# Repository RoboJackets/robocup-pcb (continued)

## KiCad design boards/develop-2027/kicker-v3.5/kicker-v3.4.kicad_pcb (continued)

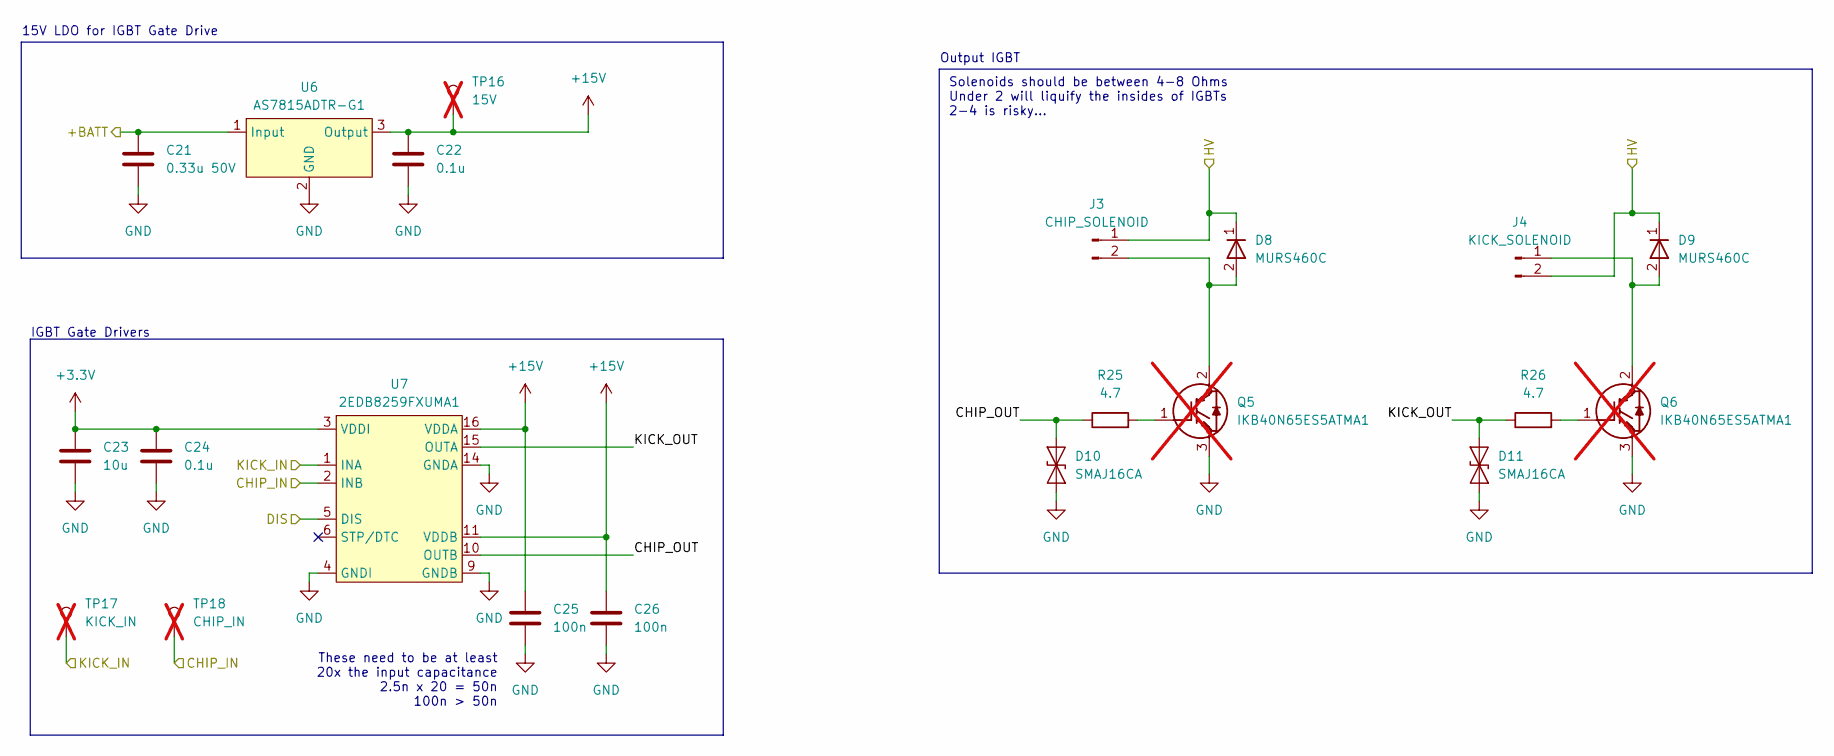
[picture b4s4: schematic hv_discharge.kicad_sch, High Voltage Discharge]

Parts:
C21: 0.33u 50V; C_0603_1608Metric; Manufacturer P/N 0603B334K500CT; LCSC P/N C296028
C22, C24: 0.1u; C_0603_1608Metric; Manufacturer P/N CL10B104KB8NNNC; LCSC P/N C1591
C23: 10u; C_0603_1608Metric; Manufacturer P/N GRM188R61E106MA73D; LCSC P/N C91606
C25, C26: 100n; C_0603_1608Metric; Manufacturer P/N CL10B104KB8NNNC; LCSC P/N C1591
D8, D9: MURS460C; D_SMC; Manufacturer P/N MURS460C; LCSC P/N C5249144
D10, D11: SMAJ16CA; D_SMA; Manufacturer P/N SMAJ16CA; LCSC P/N C19077537
J3: CHIP_SOLENOID; JST_PH_B2B-PH-K_1x02_P2.00mm_Vertical; Manufacturer P/N JST S2B-PH-K-S-GW; LCSC P/N C131337
J4: KICK_SOLENOID; JST_PH_B2B-PH-K_1x02_P2.00mm_Vertical; Manufacturer P/N JST S2B-PH-K-S-GW; LCSC P/N C131337
Q5, Q6: IKB40N65ES5ATMA1; TO-263-2; Manufacturer P/N IKB40N65ES5ATMA1; not fitted
R25, R26: 4.7; R_0603_1608Metric; Manufacturer P/N RC0603FR-074R7L; LCSC P/N C137705
TP16: 15V; TestPoint_Pad_D1.0mm; not fitted
TP17: KICK_IN; TestPoint_Pad_D1.0mm; not fitted
TP18: CHIP_IN; TestPoint_Pad_D1.0mm; not fitted
U6: AS7815ADTR-G1; TO-252-2; Manufacturer P/N AS7815ADTR-G1; LCSC P/N C460417
U7: 2EDB8259FXUMA1; SOIC-16_3.9x9.9mm_P1.27mm; Manufacturer P/N 2EDB8259FXUMA1; LCSC P/N C17317654

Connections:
+3.3V: C23.1, C24.1, U7.3 (VDDI), U7.8 (VDDI); also elsewhere on the board
+15V: C22.1, C25.1, C26.1, TP16.1 (1_1), U6.3 (Output), U7.11 (VDDB), U7.16 (VDDA)
+BATT: C21.1, U6.1 (Input); also elsewhere on the board
/Capacitor Bank/HV: D8.1 (K), D9.1 (K), J3.1, J4.2; also elsewhere on the board
/HV Discharge/CHIP_IN: TP18.1 (1_1), U7.2 (INB); also elsewhere on the board
/HV Discharge/CHIP_OUT: D10.2 (A2), R25.1, U7.10 (OUTB)
/HV Discharge/DIS: U7.5 (DIS); also elsewhere on the board
/HV Discharge/KICK_IN: TP17.1 (1_1), U7.1 (INA); also elsewhere on the board
/HV Discharge/KICK_OUT: D11.2 (A2), R26.1, U7.15 (OUTA)
GND: C21.2, C22.2, C23.2, C24.2, C25.2, C26.2, D10.1 (A1), D11.1 (A1), Q5.3 (E), Q6.3 (E), U6.2 (GND), U7.4 (GNDI), U7.9 (GNDB), U7.14 (GNDA); also elsewhere on the board
unnamed: D8.2 (A), J3.2, Q5.2 (C)
unnamed: D9.2 (A), J4.1, Q6.2 (C)
unnamed: Q5.1 (G), R25.2
unnamed: Q6.1 (G), R26.2

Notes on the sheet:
IGBT Gate Drivers
Output IGBT
15V LDO for IGBT Gate Drive
These need to be at least 20x the input capacitance 2.5n x 20 = 50n 100n > 50n
Solenoids should be between 4-8 Ohms Under 2 will liquify the insides of IGBTs 2-4 is risky...

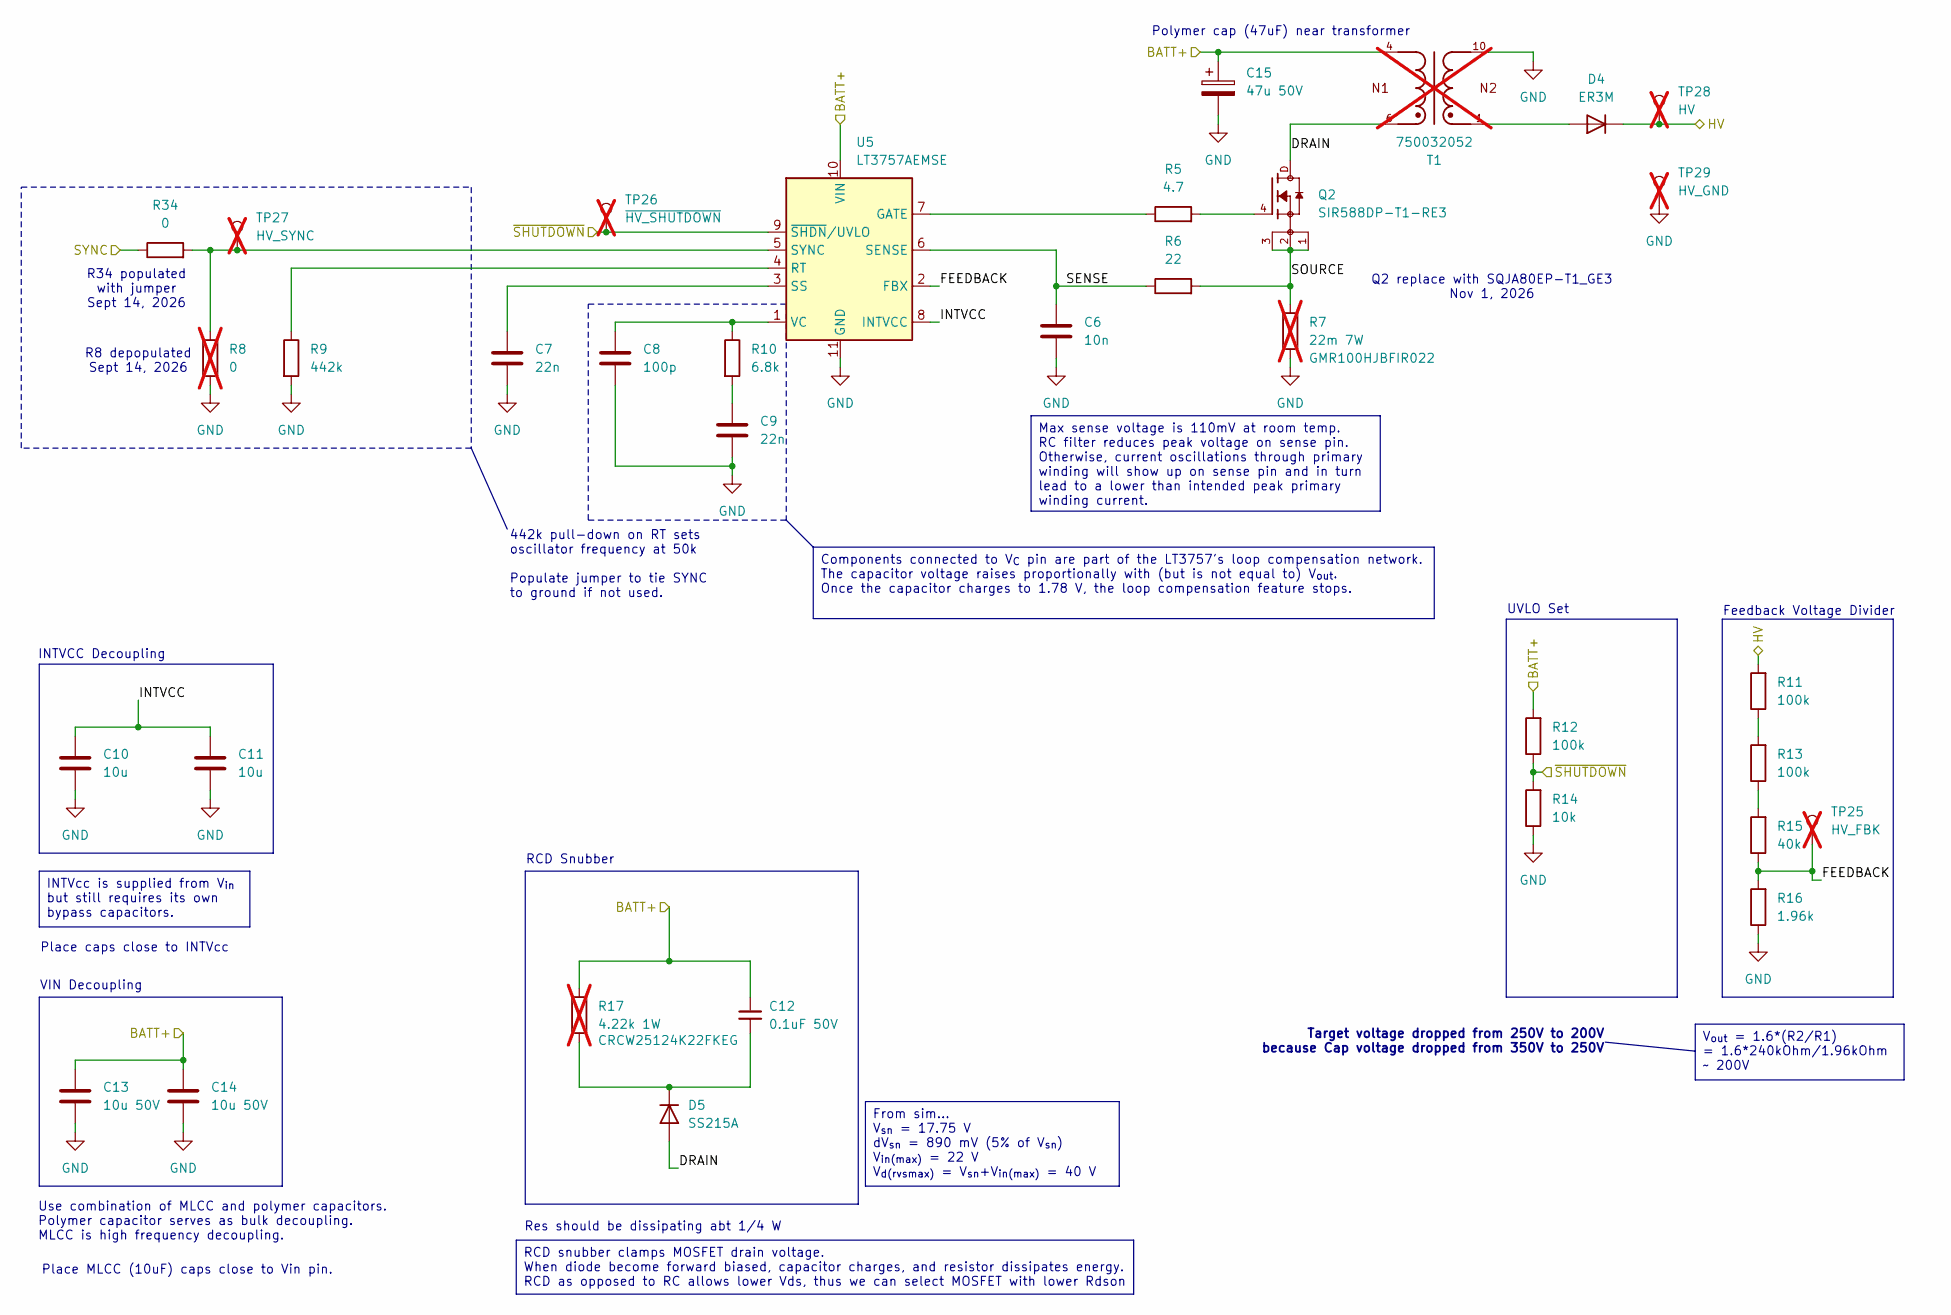
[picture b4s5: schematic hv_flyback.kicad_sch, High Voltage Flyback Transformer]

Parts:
C6: 10n; C_0603_1608Metric; Manufacturer P/N TCC0603X7R103K500CTS; LCSC P/N C880659
C7, C9: 22n; C_0603_1608Metric; Manufacturer P/N CGA3E2X7R1H223KT0Y0N; LCSC P/N C342903
C8: 100p; C_0603_1608Metric; Manufacturer P/N CL10C101JB8NNNC; LCSC P/N C14858
C10, C11: 10u; C_0603_1608Metric; Manufacturer P/N GRM188R61E106MA73D; LCSC P/N C91606
C12: 0.1uF 50V; C_1206_3216Metric; Manufacturer P/N YAGEO CC1206KKX7R0BB104; LCSC P/N C107181
C13, C14: 10u 50V; C_1206_3216Metric; Manufacturer P/N CL31A106KBHNNNE; LCSC P/N C13585
C15: 47u 50V; CP_Elec_10x10; Manufacturer P/N PCR1J470MCL1GS; LCSC P/N C3274436
D4: ER3M; D_SMC; Manufacturer P/N ER3M; LCSC P/N C152330
D5: SS215A; D_SMA; Manufacturer P/N SS215A; LCSC P/N C48996646
Q2: SIR588DP-T1-RE3; TRANS_SIR880BDPT1RE3; Manufacturer P/N SIR588DP-T1-RE3; LCSC P/N C3279540
R5: 4.7; R_0603_1608Metric; Manufacturer P/N RMCF0603FT4R70; LCSC P/N C2479773
R6: 22; R_0603_1608Metric; Manufacturer P/N RC0603FR-0722RL; LCSC P/N C107701
R7: 22m 7W; R_2512_6332Metric_Pad1.40x3.35mm_HandSolder; Manufacturer P/N GMR100HJBFIR022; not fitted
R8: 0; R_0603_1608Metric; not fitted
R9: 442k; R_0603_1608Metric; Manufacturer P/N RC0603FR-07442KL; LCSC P/N C185327
R10: 6.8k; R_0603_1608Metric; Manufacturer P/N RC0603FR-076K8L; LCSC P/N C114632
R11, R13: 100k; R_0603_1608Metric; Manufacturer P/N ERJUP3J104V; LCSC P/N C491207
R12: 100k; R_0603_1608Metric; Manufacturer P/N RC0603FR-07100KL; LCSC P/N C14675
R14: 10k; R_0603_1608Metric; Manufacturer P/N RC0603FR-0710KL; LCSC P/N C98220
R15: 40k; R_0603_1608Metric; Manufacturer P/N YAGEO RT0603BRD0740KL; LCSC P/N C861392
R16: 1.96k; R_0603_1608Metric; Manufacturer P/N FOJAN FRC0603F1961TS; LCSC P/N C2998107
R17: 4.22k 1W; R_2512_6332Metric; Manufacturer P/N CRCW25124K22FKEG; DigiKey P/N 541-4.22KAFCT-ND; not fitted
R34: 0; R_0603_1608Metric; Manufacturer P/N RC0603JR-070RL; LCSC P/N C95177
T1: 750032052; WE-FB3751_EFD20; Manufacturer P/N 750032052; LCSC P/N C17644334; not fitted
TP25: HV_FBK; TestPoint_Pad_D1.0mm; not fitted
TP26: ~{HV_SHUTDOWN}; TestPoint_Pad_D1.0mm; not fitted
TP27: HV_SYNC; TestPoint_Pad_D1.0mm; not fitted
TP28: HV; TestPoint_Pad_D1.0mm; not fitted
TP29: HV_GND; TestPoint_Pad_D1.0mm; not fitted
U5: LT3757AEMSE; MSOP-10-1EP_3x3mm_P0.5mm_EP1.68x1.88mm; Manufacturer P/N LT3757AEMSE; LCSC P/N C671465

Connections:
+BATT: C12.1, C13.1, C14.1, C15.1, R12.2, R17.1, T1.4, T1.5, U5.10 (VIN); also elsewhere on the board
/Capacitor Bank/HV: D4.1 (K), R11.2, TP28.1 (1_1); also elsewhere on the board
/HV Flyback/DRAIN: D5.2 (A), Q2.D, T1.6, T1.7
/HV Flyback/FEEDBACK: R15.1, R16.2, TP25.1 (1_1), U5.2 (FBX)
/HV Flyback/INTVCC: C10.1, C11.1, U5.8 (INTVCC)
/HV Flyback/SENSE: C6.1, R6.1, U5.6 (SENSE)
/HV Flyback/SOURCE: Q2.1, Q2.2, Q2.3, R6.2, R7.1
/HV Flyback/SYNC: R34.1; also elsewhere on the board
/HV Flyback/~SHUTDOWN: R12.1, R14.2, TP26.1 (1_1), U5.9 (~SHDN/UVLO); also elsewhere on the board
GND: C6.2, C7.2, C8.2, C9.2, C10.2, C11.2, C13.2, C14.2, C15.2, R7.2, R8.2, R9.2, R14.1, R16.1, T1.10, TP29.1 (1_1), U5.11 (GND); also elsewhere on the board
unnamed: C9.1, R10.2
unnamed: D4.2 (A), T1.1
unnamed: C12.2, D5.1 (K), R17.2
unnamed: Q2.4, R5.2
unnamed: R11.1, R13.2
unnamed: R13.1, R15.2
unnamed: R5.1, U5.7 (GATE)
unnamed: R9.1, U5.4 (RT)
unnamed: C7.1, U5.3 (SS)
unnamed: R8.1, R34.2, TP27.1 (1_1), U5.5 (SYNC)
unnamed: C8.1, R10.1, U5.1 (VC)

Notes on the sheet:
Place MLCC (10uF) caps close to Vin pin.
Feedback Voltage Divider
INTVCC Decoupling
R34 populated with jumper Sept 14, 2026
Place caps close to INTVcc
Polymer cap (47uF) near transformer
R8 depopulated Sept 14, 2026
VIN Decoupling
UVLO Set
Q2 replace with SQJA80EP-T1_GE3 Nov 1, 2026
442k pull-down on RT sets oscillator frequency at 50k Populate jumper to tie SYNC to ground if not used.
RCD Snubber
Use combination of MLCC and polymer capacitors. Polymer capacitor serves as bulk decoupling. MLCC is high frequency decoupling.
Res should be dissipating abt 1/4 W
Target voltage dropped from 250V to 200V because Cap voltage dropped from 350V to 250V
Components connected to V_{C} pin are part of the LT3757's loop compensation network. The capacitor voltage raises proportionally with (but is not equal to) V_{out}. Once the capacitor charges to 1.78 V, the loop compensation feature stops.
Max sense voltage is 110mV at room temp. RC filter reduces peak voltage on sense pin. Otherwise, current oscillations through primary winding will show up on sense pin and in turn lead to a lower than intended peak primary winding current.
From sim... V_{sn} = 17.75 V dV_{sn} = 890 mV (5% of V_{sn}) V_{in(max)} = 22 V V_{d(rvsmax)} = V_{sn}+V_{in(max)} = 40 V
V_{out} = 1.6*(R2/R1) = 1.6*240kOhm/1.96kOhm ~ 200V
INTVcc is supplied from V_{in} but still requires its own bypass capacitors.
RCD snubber clamps MOSFET drain voltage. When diode become forward biased, capacitor charges, and resistor dissipates energy. RCD as opposed to RC allows lower Vds, thus we can select MOSFET with lower Rdson

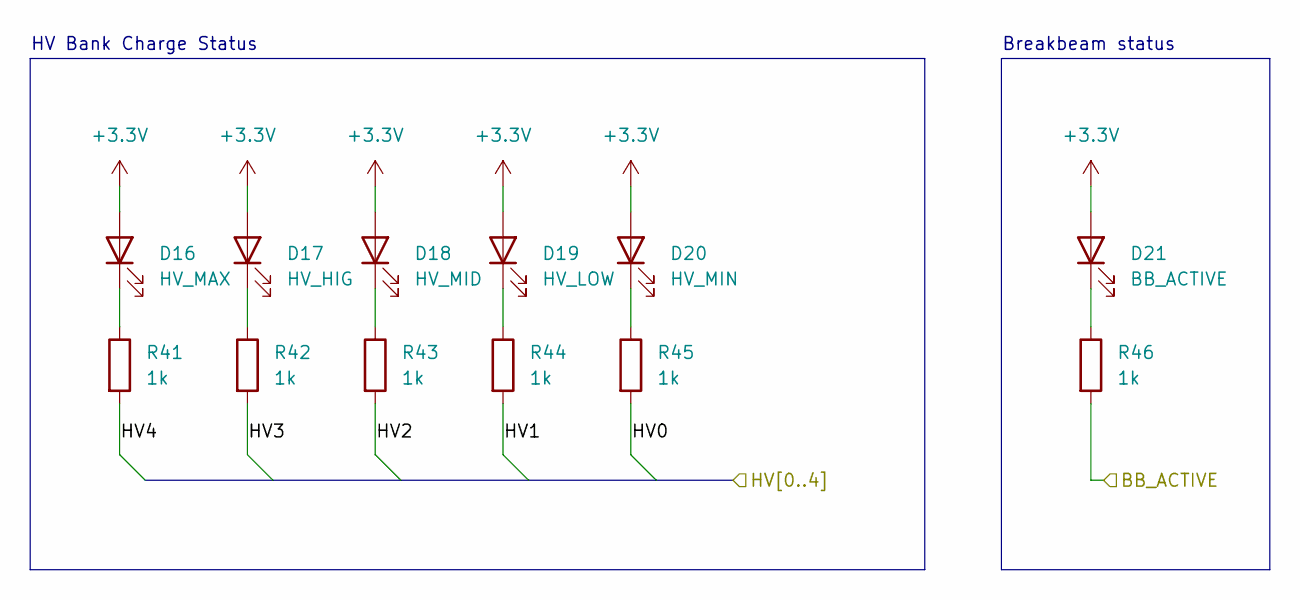
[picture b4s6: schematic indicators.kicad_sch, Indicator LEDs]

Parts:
D16: HV_MAX; LED_0603_1608Metric; Manufacturer P/N XL-1608UGC-04; LCSC P/N C965804
D17: HV_HIG; LED_0603_1608Metric; Manufacturer P/N XL-TD1608UYC; LCSC P/N C965850
D18: HV_MID; LED_0603_1608Metric; Manufacturer P/N XL-1608UGC-04; LCSC P/N C965804
D19: HV_LOW; LED_0603_1608Metric; Manufacturer P/N XL-1608UGC-04; LCSC P/N C965804
D20: HV_MIN; LED_0603_1608Metric; Manufacturer P/N XL-1608UGC-04; LCSC P/N C965804
D21: BB_ACTIVE; LED_0603_1608Metric; Manufacturer P/N XL-1608UGC-04; LCSC P/N C965804
R41, R42, R43, R44, R45, R46: 1k; R_0603_1608Metric; Manufacturer P/N RC0603FR-071KL; LCSC P/N C22548

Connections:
+3.3V: D16.2 (A), D17.2 (A), D18.2 (A), D19.2 (A), D20.2 (A), D21.2 (A); also elsewhere on the board
/Indicator LEDs/BB_ACTIVE: R46.2; also elsewhere on the board
/Indicator LEDs/HV0: R45.2; also elsewhere on the board
/Indicator LEDs/HV1: R44.2; also elsewhere on the board
/Indicator LEDs/HV2: R43.2; also elsewhere on the board
/Indicator LEDs/HV3: R42.2; also elsewhere on the board
/Indicator LEDs/HV4: R41.2; also elsewhere on the board
unnamed: D16.1 (K), R41.1
unnamed: D17.1 (K), R42.1
unnamed: D18.1 (K), R43.1
unnamed: D19.1 (K), R44.1
unnamed: D20.1 (K), R45.1
unnamed: D21.1 (K), R46.1

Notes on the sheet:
Breakbeam status
HV Bank Charge Status

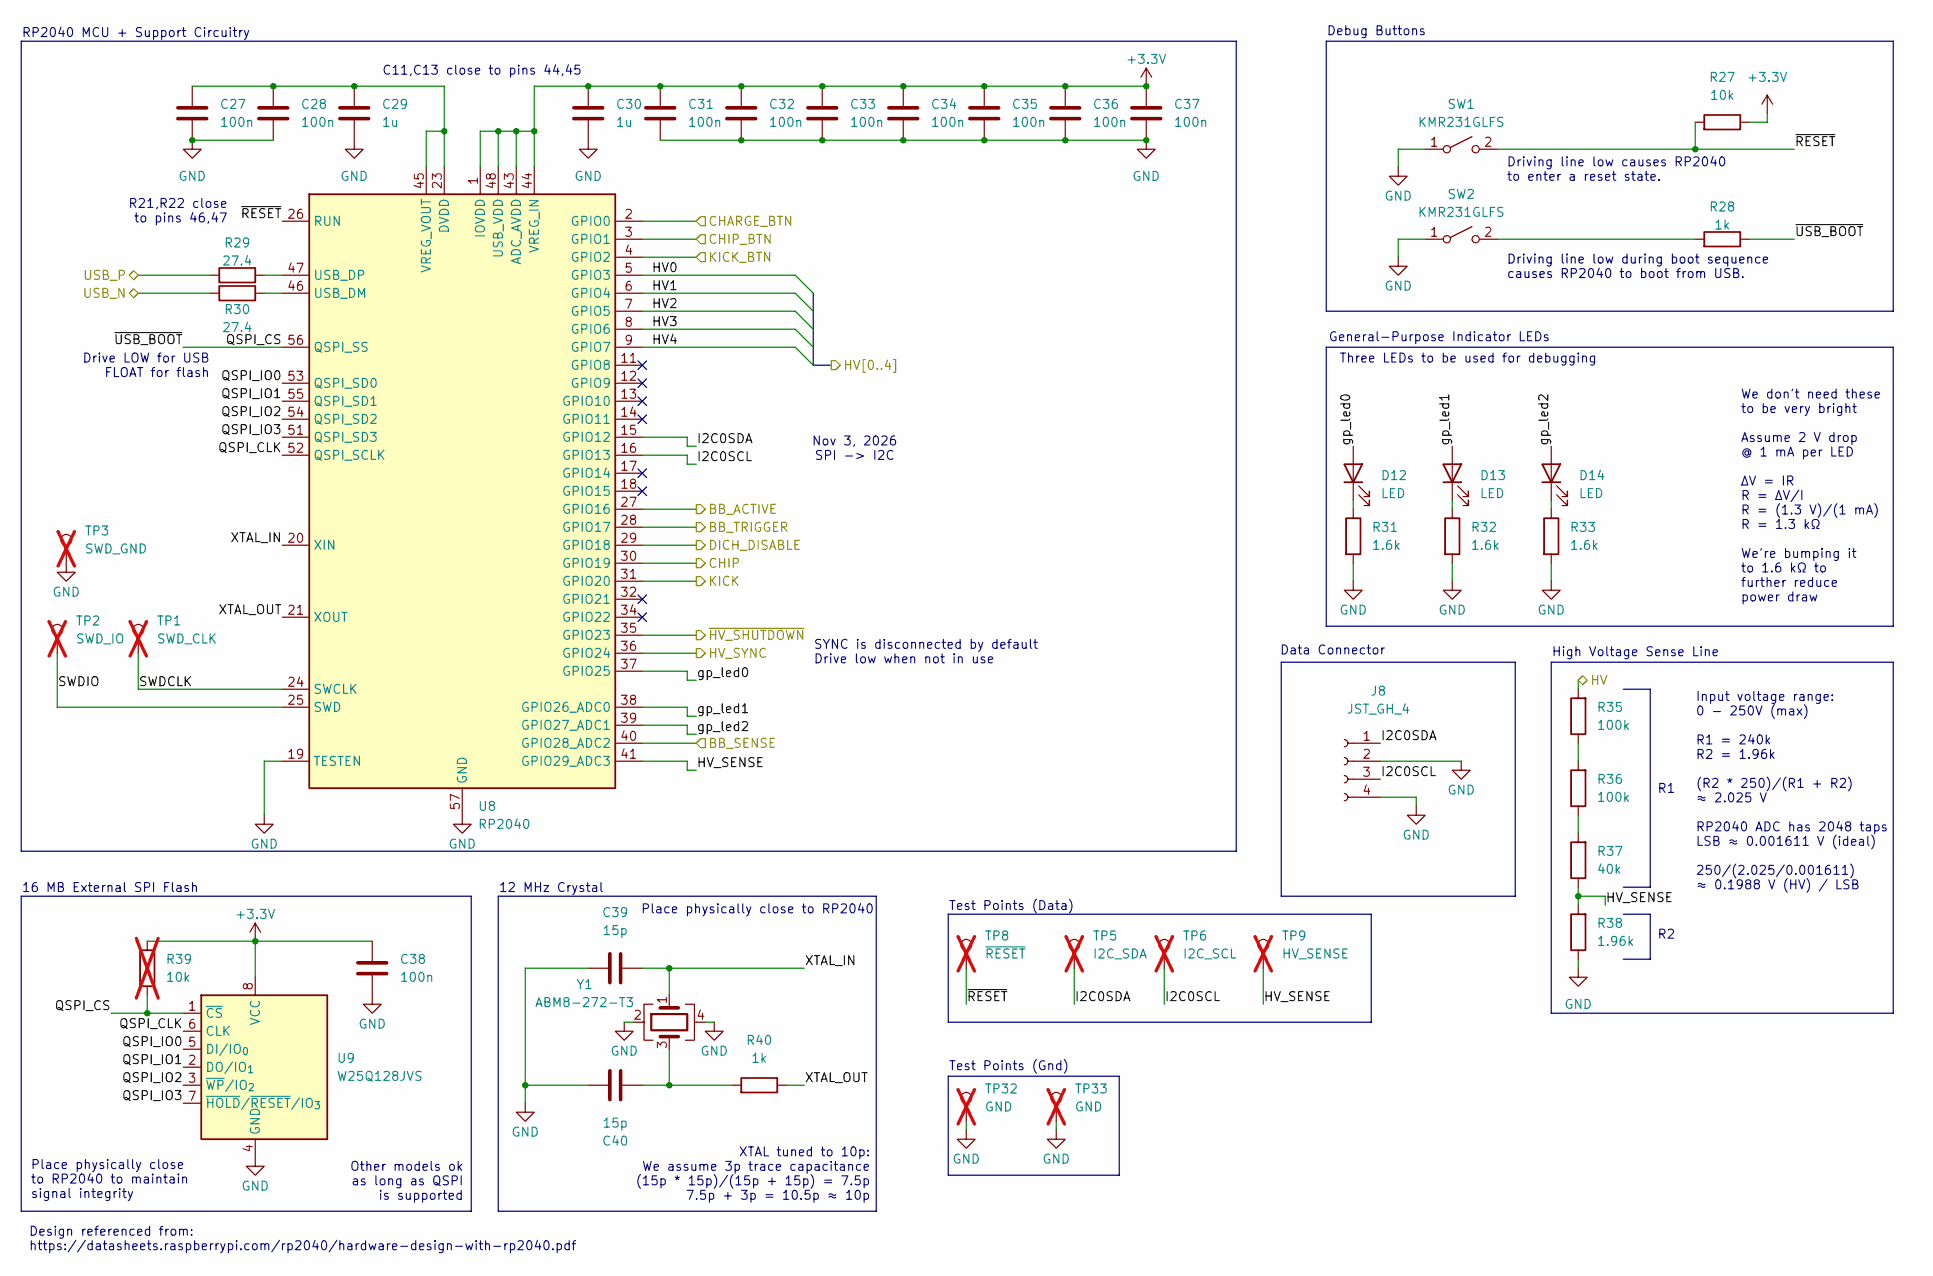
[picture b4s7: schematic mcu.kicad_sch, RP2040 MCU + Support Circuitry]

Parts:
C27, C28, C31, C32, C33, C34, C35, C36, C37: 100n; C_0402_1005Metric; Manufacturer P/N CL05B104KB5NNNC; LCSC P/N C960916
C29, C30: 1u; C_0402_1005Metric; Manufacturer P/N CL05A105KA5NQNC; LCSC P/N C52923
C38: 100n; C_0603_1608Metric; Manufacturer P/N CL10B104KB8NNNC; LCSC P/N C1591
C39, C40: 15p; C_0603_1608Metric; Manufacturer P/N CL10C150JB8NNNC; LCSC P/N C1644
D12, D13, D14: LED; LED_0603_1608Metric; Manufacturer P/N XL-1608UGC-04; LCSC P/N C965804
J8: JST_GH_4; JST_GH_SM04B-GHS-TB_1x04-1MP_P1.25mm_Horizontal; Manufacturer P/N SM04B-GHS-TB(LF)(SN); LCSC P/N C189895
R27: 10k; R_0603_1608Metric; Manufacturer P/N RC0603FR-0710KL; LCSC P/N C98220
R28: 1k; R_0603_1608Metric; Manufacturer P/N RC0603FR-071KL; LCSC P/N C22548
R29, R30: 27.4; R_0402_1005Metric; Manufacturer P/N CR0402FF27R4G; LCSC P/N C100354
R31, R32, R33: 1.6k; R_0603_1608Metric; Manufacturer P/N RC0603FR-071K6L; LCSC P/N C165489
R35, R36: 100k; R_1206_3216Metric; Manufacturer P/N RCT06100KFLF; LCSC P/N C702843
R37: 40k; R_0603_1608Metric; Manufacturer P/N YAGEO RT0603BRD0740KL; LCSC P/N C861392
R38: 1.96k; R_0603_1608Metric; Manufacturer P/N FOJAN FRC0603F1961TS; LCSC P/N C2998107
R39: 10k; R_0603_1608Metric; not fitted
R40: 1k; R_0402_1005Metric; Manufacturer P/N RC0402FR-071KL; LCSC P/N C106235
SW1, SW2: KMR231GLFS; SW_Push_1P1T_NO_CK_KMR2; Manufacturer P/N KMR231GLFS
TP1: SWD_CLK; TestPoint_THTPad_1.5x1.5mm_Drill0.7mm; not fitted
TP2: SWD_IO; TestPoint_THTPad_1.5x1.5mm_Drill0.7mm; not fitted
TP3: SWD_GND; TestPoint_THTPad_1.5x1.5mm_Drill0.7mm; not fitted
TP5: I2C_SDA; TestPoint_Pad_D1.0mm; not fitted
TP6: I2C_SCL; TestPoint_Pad_D1.0mm; not fitted
TP8: ~{RESET}; TestPoint_Pad_D1.0mm; not fitted
TP9: HV_SENSE; TestPoint_Pad_D1.0mm; not fitted
TP32, TP33: GND; TestPoint_Pad_D1.0mm; not fitted
U8: RP2040; QFN-56-1EP_7x7mm_P0.4mm_EP3.2x3.2mm; Manufacturer P/N RP2040; LCSC P/N C2040
U9: W25Q128JVS; SOIC-8_5.3x5.3mm_P1.27mm; Manufacturer P/N W25Q128JVS; LCSC P/N C97521
Y1: ABM8-272-T3; Crystal_SMD_Abracon_ABM8AIG-4Pin_3.2x2.5mm; Manufacturer P/N ABM8-272-T3; LCSC P/N C20625731

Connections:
+3.3V: C30.1, C31.1, C32.1, C33.1, C34.1, C35.1, C36.1, C37.1, C38.1, R27.1, R39.1, U8.1 (IOVDD), U8.10 (IOVDD), U8.22 (IOVDD), U8.33 (IOVDD), U8.42 (IOVDD), U8.43 (ADC_AVDD), U8.44 (VREG_IN), U8.48 (USB_VDD), U8.49 (IOVDD), U9.8 (VCC); also elsewhere on the board
/Breakbeam/BB_SENSE: U8.40 (GPIO28_ADC2); also elsewhere on the board
/Breakbeam/BB_TRIGGER: U8.28 (GPIO17); also elsewhere on the board
/Capacitor Bank/HV: R35.2; also elsewhere on the board
/Debug Buttons/CHARGE_BTN: U8.2 (GPIO0); also elsewhere on the board
/Debug Buttons/CHIP_BTN: U8.3 (GPIO1); also elsewhere on the board
/Debug Buttons/KICK_BTN: U8.4 (GPIO2); also elsewhere on the board
/HV Discharge/CHIP_IN: U8.30 (GPIO19); also elsewhere on the board
/HV Discharge/DIS: U8.29 (GPIO18); also elsewhere on the board
/HV Discharge/KICK_IN: U8.31 (GPIO20); also elsewhere on the board
/HV Flyback/SYNC: U8.36 (GPIO24); also elsewhere on the board
/HV Flyback/~SHUTDOWN: U8.35 (GPIO23); also elsewhere on the board
/Indicator LEDs/BB_ACTIVE: U8.27 (GPIO16); also elsewhere on the board
/Indicator LEDs/HV0: U8.5 (GPIO3); also elsewhere on the board
/Indicator LEDs/HV1: U8.6 (GPIO4); also elsewhere on the board
/Indicator LEDs/HV2: U8.7 (GPIO5); also elsewhere on the board
/Indicator LEDs/HV3: U8.8 (GPIO6); also elsewhere on the board
/Indicator LEDs/HV4: U8.9 (GPIO7); also elsewhere on the board
/MCU/HV_SENSE: R37.1, R38.2, TP9.1 (1_1), U8.41 (GPIO29_ADC3)
/MCU/I2C0SCL: J8.3, TP6.1 (1_1), U8.16 (GPIO13)
/MCU/I2C0SDA: J8.1, TP5.1 (1_1), U8.15 (GPIO12)
/MCU/QSPI_CLK: U8.52 (QSPI_SCLK), U9.6 (CLK)
/MCU/QSPI_CS: R28.1, R39.2, U8.56 (QSPI_SS), U9.1 (~CS)
/MCU/QSPI_IO0: U8.53 (QSPI_SD0), U9.5 (DI/IO_{0})
/MCU/QSPI_IO1: U8.55 (QSPI_SD1), U9.2 (DO/IO_{1})
/MCU/QSPI_IO2: U8.54 (QSPI_SD2), U9.3 (~WP/IO_{2})
/MCU/QSPI_IO3: U8.51 (QSPI_SD3), U9.7 (~HOLD/~RESET/IO_{3})
/MCU/SWDCLK: TP1.1 (1_1), U8.24 (SWCLK)
/MCU/SWDIO: TP2.1 (1_1), U8.25 (SWD)
/MCU/USB_N: R30.1; also elsewhere on the board
/MCU/USB_P: R29.1; also elsewhere on the board
/MCU/XTAL_IN: C39.2, U8.20 (XIN), Y1.1
/MCU/XTAL_OUT: R40.1, U8.21 (XOUT)
/MCU/gp_led0: D12.2 (A), U8.37 (GPIO25)
/MCU/gp_led1: D13.2 (A), U8.38 (GPIO26_ADC0)
/MCU/gp_led2: D14.2 (A), U8.39 (GPIO27_ADC1)
/MCU/~RESET: R27.2, SW1.2 (B), TP8.1 (1_1), U8.26 (RUN)
GND: C27.2, C28.2, C29.2, C30.2, C31.2, C32.2, C33.2, C34.2, C35.2, C36.2, C37.2, C38.2, C39.1, C40.2, J8.2, J8.4, R31.2, R32.2, R33.2, R38.1, SW1.1 (A), SW2.1 (A), TP3.1 (1_1), TP32.1 (1_1), TP33.1 (1_1), U8.19 (TESTEN), U8.57 (GND), U9.4 (GND), Y1.2, Y1.4; also elsewhere on the board
unnamed: C40.1, R40.2, Y1.3
unnamed: D12.1 (K), R31.1
unnamed: D13.1 (K), R32.1
unnamed: D14.1 (K), R33.1
unnamed: R35.1, R36.2
unnamed: R36.1, R37.2
unnamed: R28.2, SW2.2 (B)
unnamed: R30.2, U8.46 (USB_DM)
unnamed: R29.2, U8.47 (USB_DP)
unnamed: C27.1, C28.1, C29.1, U8.23 (DVDD), U8.45 (VREG_VOUT), U8.50 (DVDD)

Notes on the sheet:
Other models ok as long as QSPI is supported
Nov 3, 2026 SPI -> I2C
SYNC is disconnected by default Drive low when not in use
Driving line low causes RP2040 to enter a reset state.
Test Points (Data)
Driving line low during boot sequence causes RP2040 to boot from USB.
Place physically close to RP2040
Input voltage range: 0 - 250V (max) R1 = 240k R2 = 1.96k (R2 * 250)/(R1 + R2) ≈ 2.025 V RP2040 ADC has 2048 taps LSB ≈ 0.001611 V (ideal) 250/(2.025/0.001611) ≈ 0.1988 V (HV) / LSB
Three LEDs to be used for debugging
Debug Buttons
Place physically close to RP2040 to maintain signal integrity
C11,C13 close to pins 44,45
XTAL tuned to 10p: We assume 3p trace capacitance (15p * 15p)/(15p + 15p) = 7.5p 7.5p + 3p = 10.5p ≈ 10p
R21,R22 close to pins 46,47
Data Connector
Test Points (Gnd)
General-Purpose Indicator LEDs
RP2040 MCU + Support Circuitry
High Voltage Sense Line
We don't need these to be very bright Assume 2 V drop @ 1 mA per LED ΔV = IR R = ΔV/I R = (1.3 V)/(1 mA) R = 1.3 kΩ We're bumping it to 1.6 kΩ to further reduce power draw
Drive LOW for USB FLOAT for flash
Design referenced from: https://datasheets.raspberrypi.com/rp2040/hardware-design-with-rp2040.pdf
16 MB External SPI Flash
12 MHz Crystal

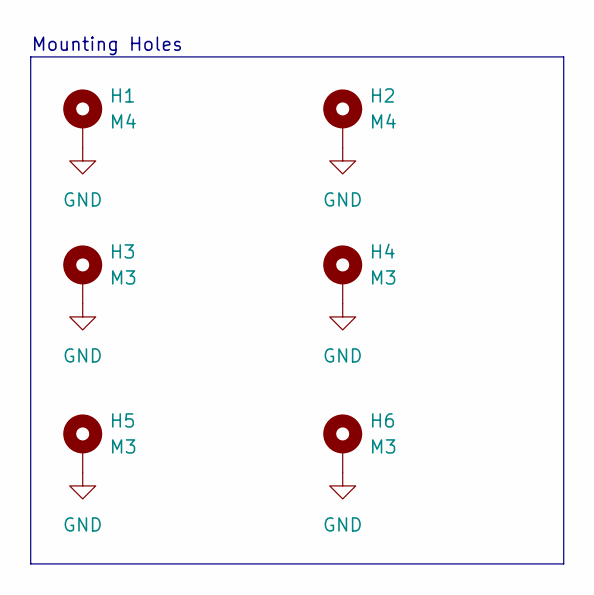
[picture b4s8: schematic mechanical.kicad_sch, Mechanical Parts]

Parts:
H1, H2: M4; MountingHole_4.3mm_M4_Pad
H3, H4, H5, H6: M3; MountingHole_3.5mm_Pad

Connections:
GND: H1.1 (1_1), H2.1 (1_1), H3.1 (1_1), H4.1 (1_1), H5.1 (1_1), H6.1 (1_1); also elsewhere on the board

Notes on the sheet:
Mounting Holes

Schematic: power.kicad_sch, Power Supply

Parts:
C1: 2.2u 50V; C_0603_1608Metric; Manufacturer P/N UMK107BBJ225KA-T; LCSC P/N C268016
C2: 22u; C_0805_2012Metric_Pad1.18x1.45mm_HandSolder; Manufacturer P/N CL21A226MAYNNNE; LCSC P/N C602037
C3, C4: 1u; C_0603_1608Metric; Manufacturer P/N CL10A105KB8NNNC; LCSC P/N C15849
C5: 10u; C_0603_1608Metric; Manufacturer P/N GRM188R61E106MA73D; LCSC P/N C91606
D1: SMBJ20A; D_SMB; Manufacturer P/N SMBJ20A; LCSC P/N C19077575
D2, D3: TPD1E04U04DPYR; D_0402_1005Metric; Manufacturer P/N TPD1E04U04DPYR; LCSC P/N C19829541
F1: 01530007Z; FUSE_01530007Z; Manufacturer P/N 01530007Z; LCSC P/N C206906
J1: JST_PH; JST_PH_S4B-PH-K_1x04_P2.00mm_Horizontal; Manufacturer P/N S4B-PH-K-S; LCSC P/N C157926
J2: 12402012E212A; AMPHENOL_12402012E212A; Manufacturer P/N 12402012E212A; LCSC P/N C5150972
L1: 10u 540mA; L_1210_3225Metric; Manufacturer P/N LBC3225T100KR; LCSC P/N C223424
Q1: SUM70101EL-GE3; TO-263-2; Manufacturer P/N SUM70101EL-GE3; LCSC P/N C5156028
R1: 100k; R_0603_1608Metric; Manufacturer P/N RC0603FR-07100KL; LCSC P/N C14675
R2: 1k; R_0603_1608Metric; Manufacturer P/N RC0603FR-071KL; LCSC P/N C22548
R3, R4: 5.1k; R_0603_1608Metric; Manufacturer P/N RC0603FR-075K1L; LCSC P/N C105580
TP19: VBATT; TestPoint_Pad_D1.0mm; not fitted
TP20: PROT_BYPASS; TestPoint_Pad_D1.0mm; not fitted
TP21: 3.3V DEBUG; TestPoint_Pad_D1.0mm; not fitted
TP22: 3.3V_REG; TestPoint_Pad_D1.0mm; not fitted
TP23: 3.3V; TestPoint_Pad_D1.0mm; not fitted
TP24: VBUS; TestPoint_Pad_D1.0mm; not fitted
U1: TPS62177DQC; WSON-10-1EP_2x3mm_P0.5mm_EP0.84x2.4mm; Manufacturer P/N TPS62177DQC; LCSC P/N C91241
U2: TLV75733PDBV; SOT-23-5; Manufacturer P/N TLV75733PDBV; LCSC P/N C485517
U3, U4: LM66100DCK; SOT-363_SC-70-6; Manufacturer P/N LM66100DCK; LCSC P/N C2869734

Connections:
+3.3V: C5.1, TP23.1 (1_1), U3.6 (VOUT), U4.6 (VOUT); also elsewhere on the board
+BATT: C1.1, D1.1 (K), Q1.2 (D), TP19.1 (1_1), U1.2 (VIN), U1.3 (EN); also elsewhere on the board
/MCU/USB_N: D3.1 (A1), J2.A7 (D-_A), J2.B7 (D-_B); also elsewhere on the board
/MCU/USB_P: D2.1 (A1), J2.A6 (D+_A), J2.B6 (D+_B); also elsewhere on the board
/Power/3.3V_DEBUG: C4.1, R2.1, TP21.1 (1_1), U2.5 (OUT), U3.1 (VIN)
/Power/3.3V_REG: C2.1, L1.2, R1.1, TP22.1 (1_1), U1.8 (~SLEEP), U1.10 (VOS), U3.3 (~CE), U4.1 (VIN)
GND: C1.2, C2.2, C3.2, C4.2, C5.2, D1.2 (A), D2.2 (A2), D3.2 (A2), J1.1, J1.2, J2.A1_B12 (GND), J2.B1_A12 (GND), J2.SH1 (SHIELD), J2.SH2 (SHIELD), J2.SH3 (SHIELD), J2.SH4 (SHIELD), Q1.1 (G), R3.2, R4.2, U1.1 (PGND), U1.4 (NC), U1.5 (FB), U1.6 (AGND), U1.11 (PAD), U2.2 (GND), U3.2 (GND), U4.2 (GND), U4.5 (ST); also elsewhere on the board
unnamed: F1.1, J1.3, J1.4, TP20.1 (1_1)
unnamed: J2.A5 (CC1_A), R3.1
unnamed: J2.B5 (CC1_B), R4.1
unnamed: F1.2, Q1.3 (S)
unnamed: R1.2, U1.7 (PG)
unnamed: L1.1, U1.9 (SW)
unnamed: R2.2, U3.5 (ST), U4.3 (~CE)
VBUS: C3.1, J2.A4_B9 (VBUS), J2.B4_A9 (VBUS), TP24.1 (1_1), U2.1 (IN), U2.3 (EN)

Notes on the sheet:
Most components are 50A rated EXCEPT the fuse holder and the DA2034 inductor. The inductor is rated for continuous operation of 10A, however the current design of the board does not operate at continuous current.
3.3V 1A Low-Dropout Regulator (USB only)
Reverse polarity prot. not needed. If USB power is flipped you have bigger problems.
20.0 V Standoff 32.4 V Clamp
This isn't strictly nessesary, but it's additional protection for USB/SWD
Debug is either SWD or USB
This PFET configuration is typical of a reverse polarity protection circuit. It isn't broken. There are a few blogs/videos on this just search "PFET reverse polarity protection".
NOTE: Spec fuse based on the reverse current protection FET and diode on this sheet as well as the max switching current of Q1, T1, and D1 on the LT3751 sheet. The LT3751 current sense resistors should be set to limit current below the limit of the fuse.
Use 15 A
FB is not used on the *62177 since it's a fixed 3.3V version of the *62155
Expected current draw, 3.3V Maximum Current Draw: 40 mA - RP2040 MCU 160 mA - 16 x LED @ 10 mA ea. 100 mA - Budget for Breakbeam 400 mA < 500 mA (Reg. Limit)
Power Input with Reverse Polarity Protection
Nom switching freq. 1 MHz
Connect directly to VOUT if possible Regulator always on
3.3V 500 mA Switching Regulator
3.3V Dual-Supply ORing Power Mux
5.1k pull-down on CC1/2 generally makes sure the host gives AT LEAST 500 mA if USB 2+ compliant.
We use a switching regulator for +BATT to 3.3V because the LDOs are much less efficient than switching regulators for this voltage difference. (≈16.5% vs >80% for 20V +BATT) However, LDOs are acceptable for 5V to 3.3V step-down because this rail is only used for debugging and LDOs are far more effi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
USB-C Connector

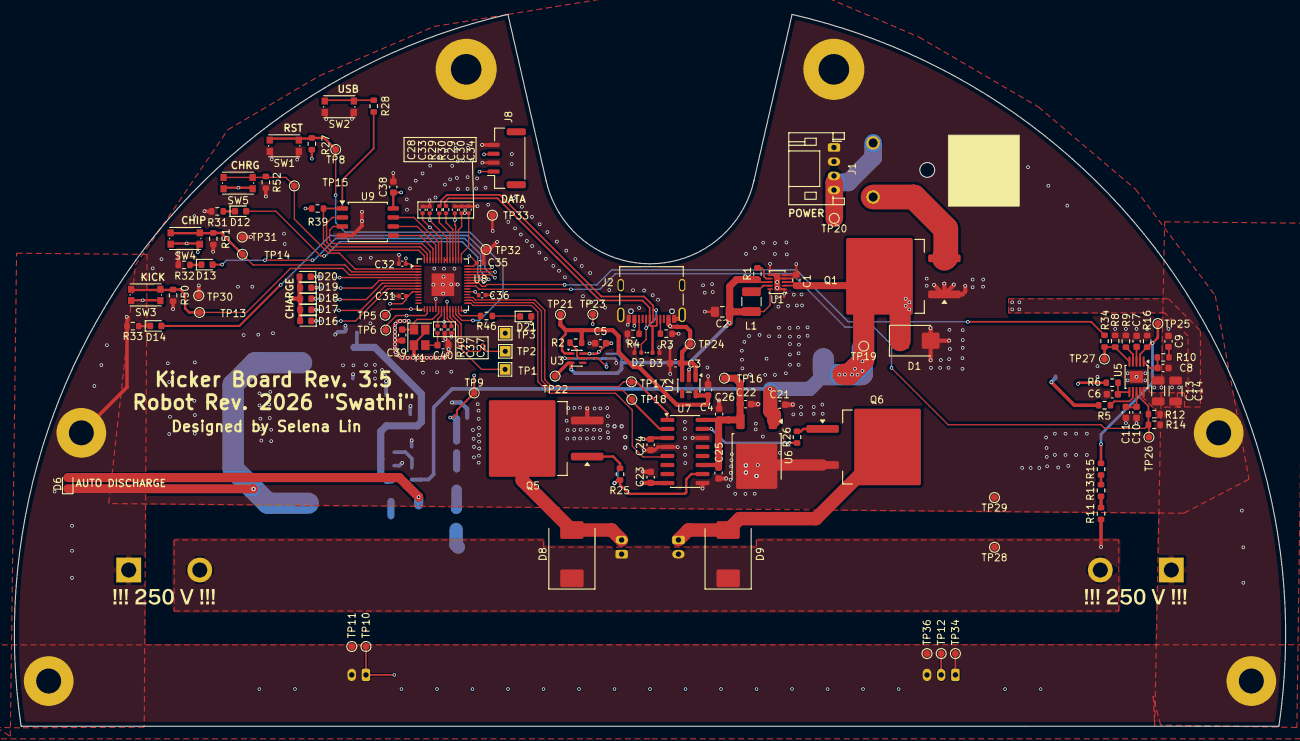
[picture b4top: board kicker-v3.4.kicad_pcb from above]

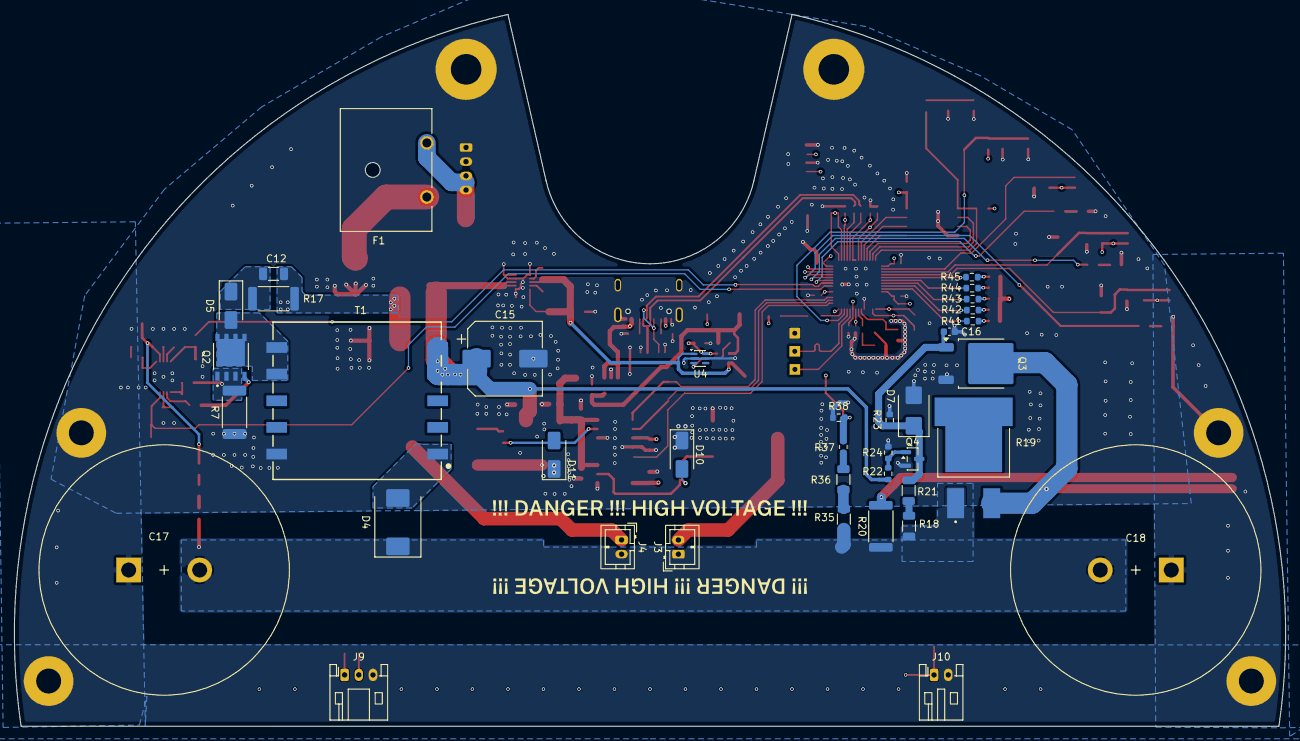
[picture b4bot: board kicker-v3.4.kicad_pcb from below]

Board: 4 copper layers, 179.0 x 100.2 mm, 177 parts (38 on the bottom side), 93 nets.

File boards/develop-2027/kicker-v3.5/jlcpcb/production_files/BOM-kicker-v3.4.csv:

Comment,Designator,Footprint,LCSC,Quantity
0,R34,R_0603_1608Metric,C95177,1
0.1u,"C22,C24",C_0603_1608Metric,C1591,2
0.1u 50V,C16,C_0603_1608Metric,C1591,1
0.1uF 50V,C12,C_1206_3216Metric,C107181,1
0.33u 50V,C21,C_0603_1608Metric,C296028,1
01530007Z,F1,FUSE_01530007Z,C206906,1
1.6k,"R31,R32,R33",R_0603_1608Metric,C165489,3
1.96k,"R16,R38",R_0603_1608Metric,C2998107,2
100k,"R1,R12,R24",R_0603_1608Metric,C14675,3
100k,"R11,R13",R_0603_1608Metric,C491207,2
100k,"R35,R36",R_1206_3216Metric,C702843,2
100n,"C25,C26,C38",C_0603_1608Metric,C1591,3
100n,"C27,C28,C31,C32,C33,C34,C35,C36,C37",C_0402_1005Metric,C960916,9
100p,C8,C_0603_1608Metric,C14858,1
10k,"R14,R27,R50,R51,R52",R_0603_1608Metric,C98220,5
10n,C6,C_0603_1608Metric,C880659,1
10u,"C10,C11,C23,C5",C_0603_1608Metric,C91606,4
10u 50V,"C13,C14",C_1206_3216Metric,C13585,2
10u 540mA,L1,L_1210_3225Metric,C223424,1
12402012E212A,J2,AMPHENOL_12402012E212A,C5150972,1
15p,"C39,C40",C_0603_1608Metric,C1644,2
1k,R40,R_0402_1005Metric,C106235,1
1k,"R2,R28,R41,R42,R43,R44,R45,R46",R_0603_1608Metric,C22548,8
1u,"C3,C4",C_0603_1608Metric,C15849,2
1u,"C29,C30",C_0402_1005Metric,C52923,2
2.2u 50V,C1,C_0603_1608Metric,C268016,1
22,R6,R_0603_1608Metric,C107701,1
22n,"C7,C9",C_0603_1608Metric,C342903,2
22u,C2,C_0805_2012Metric_Pad1.18x1.45mm_HandSolder,C602037,1
27.4,"R29,R30",R_0402_1005Metric,C100354,2
270k,R22,R_0603_1608Metric,C137755,1
270k,R20,R_2512_6332Metric,C2775917,1
2EDB8259FXUMA1,U7,SOIC-16_3.9x9.9mm_P1.27mm,C17317654,1
4.7,"R25,R26",R_0603_1608Metric,C137705,2
4.7,R5,R_0603_1608Metric,C2479773,1
40k,"R15,R37",R_0603_1608Metric,C861392,2
442k,R9,R_0603_1608Metric,C185327,1
47u 50V,C15,CP_Elec_10x10,C3274436,1
5.1M,"R18,R21",R_1206_3216Metric,C185741,2
5.1k,"R3,R4",R_0603_1608Metric,C105580,2
6.8k,R10,R_0603_1608Metric,C114632,1
ABM8-272-T3,Y1,Crystal_SMD_Abracon_ABM8AIG-4Pin_3.2x2.5mm,C20625731,1
AS7815ADTR-G1,U6,TO-252-2,C460417,1
BB_ACTIVE,D21,LED_0603_1608Metric,C965804,1
BB_RX,J10,JST_PH_S2B-PH-K_1x02_P2.00mm_Horizontal,C2982155,1
BB_TX,J9,JST_PH_S3B-PH-K_1x03_P2.00mm_Horizontal,C2982156,1
BSS127S,Q4,SOT-23,C154890,1
CHIP_SOLENOID,J3,JST_PH_B2B-PH-K_1x02_P2.00mm_Vertical,C131337,1
ER3M,D4,D_SMC,C668919,1
HV_HIG,D17,LED_0603_1608Metric,C965799,1
HV_LOW,D19,LED_0603_1608Metric,C965804,1
HV_MAX,D16,LED_0603_1608Metric,C965799,1
HV_MID,D18,LED_0603_1608Metric,C125094,1
HV_MID,D6,LED_0603_1608Metric,C965799,1
HV_MIN,D20,LED_0603_1608Metric,C965804,1
JST_GH_4,J8,JST_GH_SM04B-GHS-TB_1x04-1MP_P1.25mm_Horizontal,C189895,1
JST_PH,J1,JST_PH_S4B-PH-K_1x04_P2.00mm_Horizontal,C157926,1
KICK_SOLENOID,J4,JST_PH_B2B-PH-K_1x02_P2.00mm_Vertical,C131337,1
LED,"D12,D13,D14",LED_0603_1608Metric,C965804,3
LM66100DCK,"U3,U4",SOT-363_SC-70-6,C2869734,2
LT3757AEMSE,U5,MSOP-10-1EP_3x3mm_P0.5mm_EP1.68x1.88mm,C671465,1
MURS460C,"D8,D9",D_SMC,C5249144,2
RP2040,U8,QFN-56-1EP_7x7mm_P0.4mm_EP3.2x3.2mm,C2040,1
SIR588DP-T1-RE3,Q2,TRANS_SIR880BDPT1RE3,C3279540,1
SMAJ16CA,"D10,D11",D_SMA,C19077537,2
SMBJ20A,D1,D_SMB,C19077575,1
SS215A,D5,D_SMA,C48996646,1
STD1NK60T4,Q3,TO-252-2,C361030,1
SUM70101EL-GE3,Q1,TO-263-2,C5156028,1
TLV75733PDBV,U2,SOT-23-5,C485517,1
TPD1E04U04DPYR,"D2,D3",D_0402_1005Metric,C19829541,2
TPS62177DQC,U1,WSON-10-1EP_2x3mm_P0.5mm_EP0.84x2.4mm,C91241,1
W25Q128JVS,U9,SOIC-8_5.3x5.3mm_P1.27mm,C97521,1
KMR231GLFS,SW5,SW_Push_1P1T_NO_CK_KMR2,,1
KMR231GLFS,SW4,SW_Push_1P1T_NO_CK_KMR2,,1
KMR231GLFS,SW3,SW_Push_1P1T_NO_CK_KMR2,,1
KMR231GLFS,SW2,SW_Push_1P1T_NO_CK_KMR2,,1
KMR231GLFS,SW1,SW_Push_1P1T_NO_CK_KMR2,,1
